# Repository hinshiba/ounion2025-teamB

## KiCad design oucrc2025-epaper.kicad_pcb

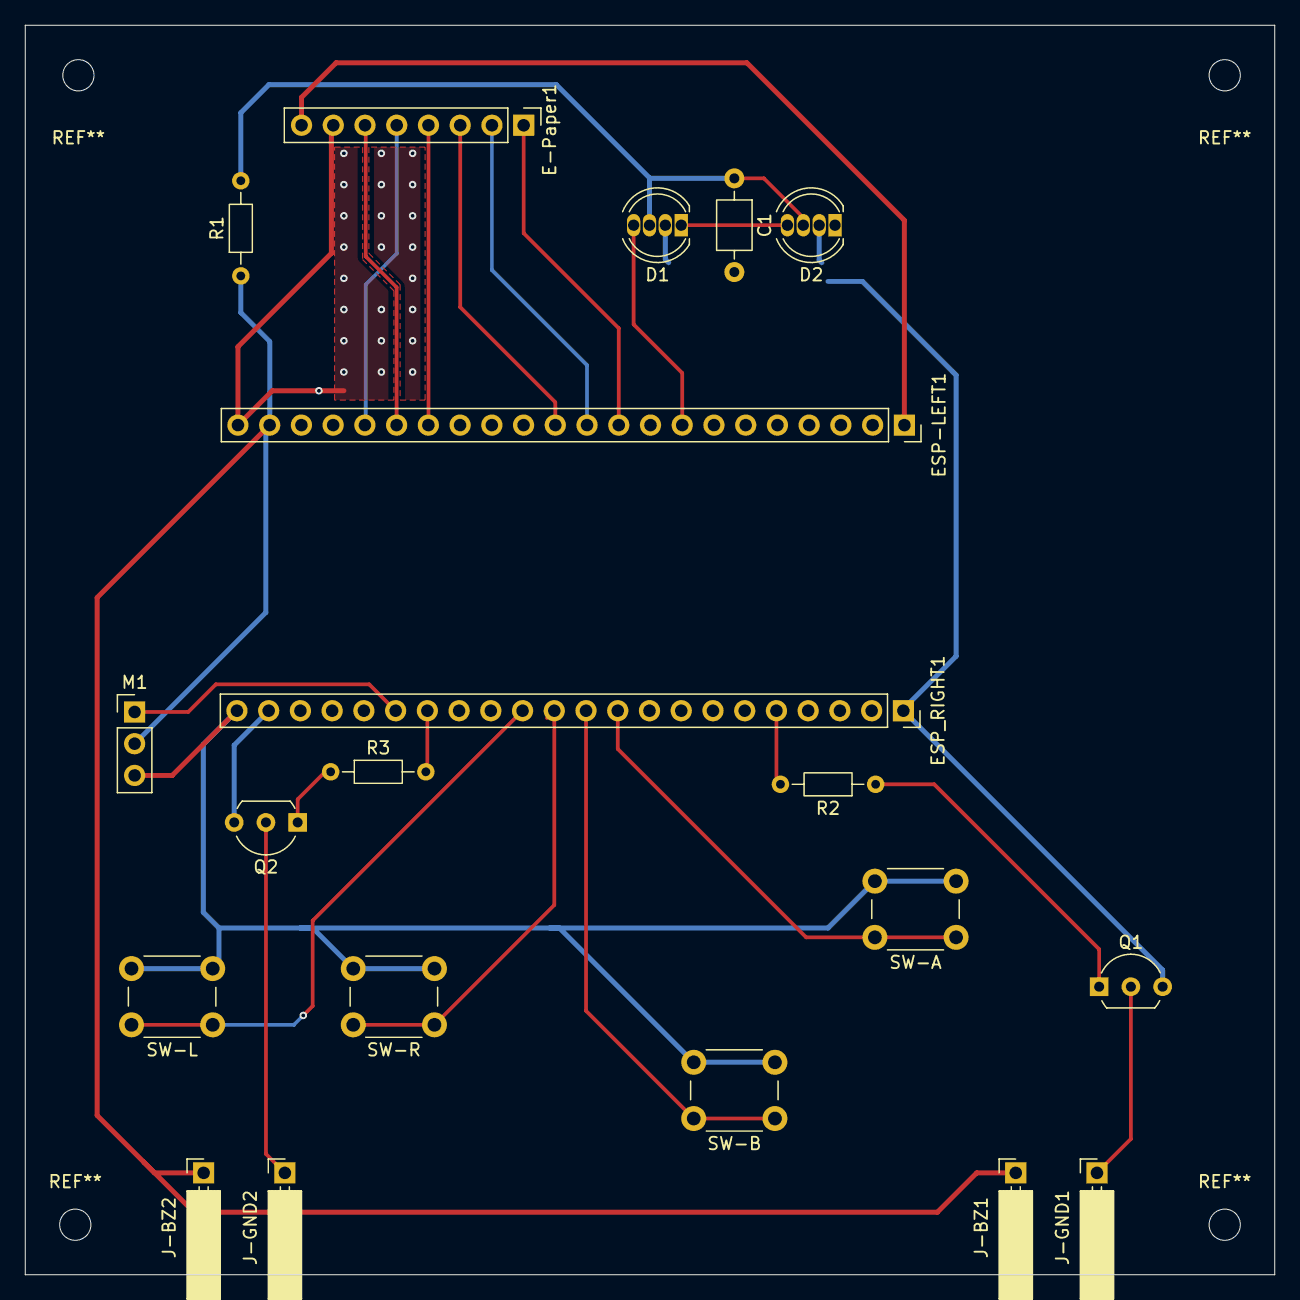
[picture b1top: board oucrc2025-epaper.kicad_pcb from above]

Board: 2 copper layers, 100.0 x 100.0 mm, 20 parts (0 on the bottom side), 23 nets.

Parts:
C1: C; C_Axial_L3.8mm_D2.6mm_P7.50mm_Horizontal
D1, D2: NeoPixel_THT; LED_D5.0mm-4_RGB
E-Paper1: Conn_01x08_Socket; PinHeader_1x08_P2.54mm_Vertical
ESP-LEFT1: Conn_01x22_Socket; PinSocket_1x22_P2.54mm_Vertical
ESP_RIGHT1: Conn_01x22_Socket; PinSocket_1x22_P2.54mm_Vertical
J-BZ1, J-BZ2: Conn_01x01_Socket; PinSocket_1x01_P2.54mm_Horizontal
J-GND1, J-GND2: Conn_01x01_Socket; PinSocket_1x01_P2.54mm_Horizontal
M1: Motor_Servo; PinHeader_1x03_P2.54mm_Vertical
Q1, Q2: 2SC2240GR; TO-92L_Inline_Wide
R1: 150; R_Axial_DIN0204_L3.6mm_D1.6mm_P7.62mm_Horizontal
R2, R3: 10k; R_Axial_DIN0204_L3.6mm_D1.6mm_P7.62mm_Horizontal
SW-A: SW_Push; SW_PUSH_6mm
SW-B: SW_Push; SW_PUSH_6mm
SW-L: SW_Push; SW_PUSH_6mm
SW-R: SW_Push; SW_PUSH_6mm

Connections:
+3V3: E-Paper1.8, ESP-LEFT1.1
+5V: ESP-LEFT1.21, J-BZ1.1, J-BZ2.1, M1.2 (+), R1.1
/BUSY: E-Paper1.1, ESP-LEFT1.10
/CS: E-Paper1.4, ESP-LEFT1.16
/D/C: E-Paper1.3, ESP-LEFT1.12
/MOSI: E-Paper1.6, ESP-LEFT1.17
/PWM: ESP_RIGHT1.17, M1.1 (PWM)
/RES: E-Paper1.2, ESP-LEFT1.11
/SCL: E-Paper1.5, ESP-LEFT1.18
/led: D1.4 (DIN), ESP-LEFT1.8
/push1: ESP_RIGHT1.10, SW-A.1
/push2: ESP_RIGHT1.11, SW-B.1
/push3: ESP_RIGHT1.12, SW-R.1
/push4: ESP_RIGHT1.13, SW-L.1
/sound1: ESP_RIGHT1.5, R2.2
/sound2: ESP_RIGHT1.16, R3.2
GND: C1.2, D1.2 (GND), D2.2 (GND), E-Paper1.7, ESP-LEFT1.22, ESP_RIGHT1.1, ESP_RIGHT1.21, ESP_RIGHT1.22, M1.3 (-), Q1.3 (E), Q2.3 (E), SW-A.2, SW-B.2, SW-L.2, SW-R.2
unnamed: D1.1 (DOUT), D2.4 (DIN)
unnamed: C1.1, D1.3 (VDD), D2.3 (VDD), R1.2
unnamed: J-GND1.1, Q1.2 (B)
unnamed: J-GND2.1, Q2.2 (B)
unnamed: Q1.1 (C), R2.1
unnamed: Q2.1 (C), R3.1

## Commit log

2025-10-13 feat: かなり進捗
2025-10-13 fix: コネクタの位置を修正していなかった
2025-10-30 init
2025-10-30 feat: なんか動く
2025-10-31 feat: タスク待機
2025-10-31 feat: UIの状態管理
2025-10-31 fix: 更新されないバグを修正
2025-10-31 fix: さらにいくつかのバグを修正
2025-10-31 feat: rgbLED追加
2025-10-31 feat: 画像の追加
